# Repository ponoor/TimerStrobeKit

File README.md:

# TimerStrobeKit
A simple Arduino shield for timer and strobe

### BOM list
https://docs.google.com/spreadsheets/d/1uPikIjkAWC3uok0h-zIkFJXL1ukJnj77JqhKgZAHLNc/edit?usp=sharing

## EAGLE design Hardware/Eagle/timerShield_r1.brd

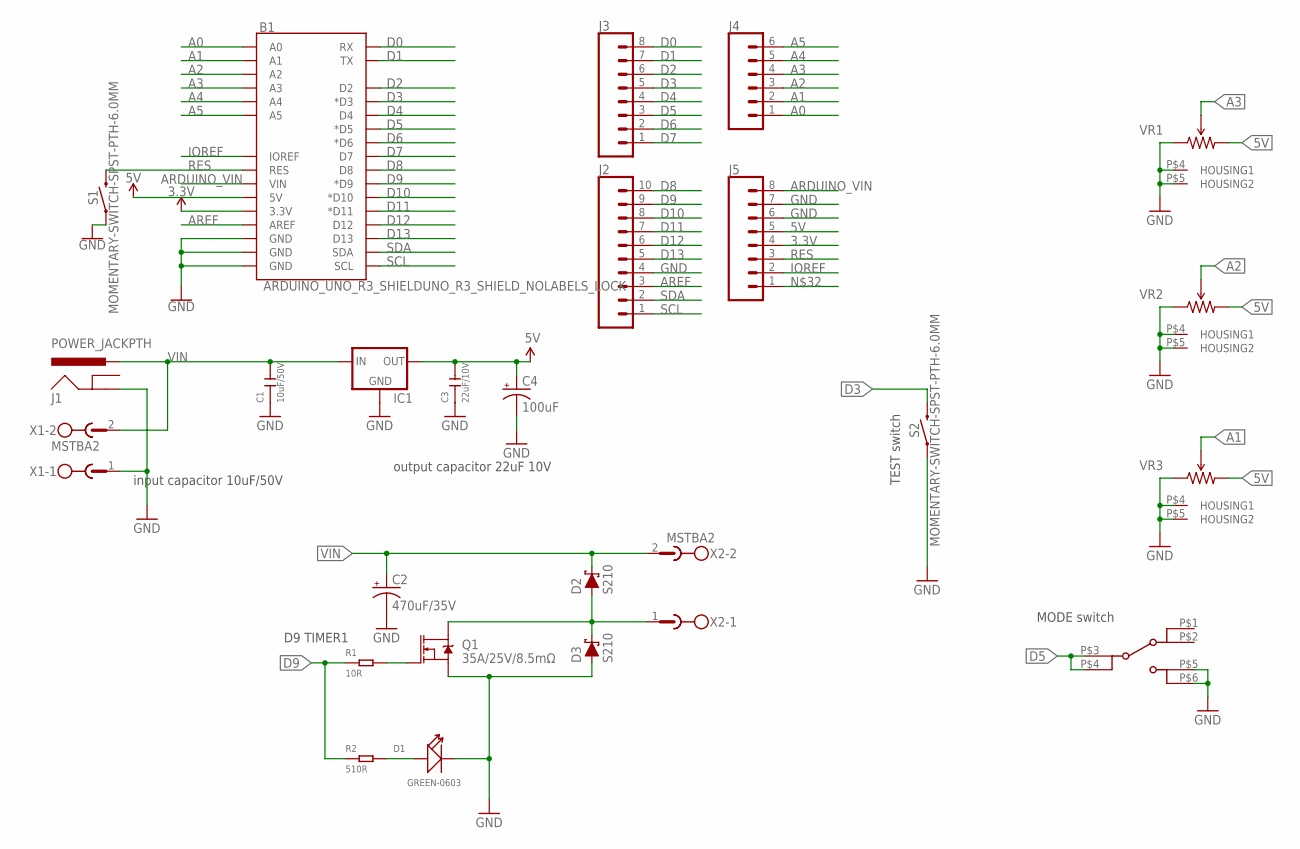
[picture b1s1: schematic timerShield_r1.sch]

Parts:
B1: ARDUINO_UNO_R3_SHIELDUNO_R3_SHIELD_NOLABELS_LOCK; UNO_R3_SHIELD_NOLABELS_LOCK
C1: 10uF/50V; C1206
C2: 470uF/35V; CPOL-RADIAL-5MM-10MM-KIT
C3: 22uF/10V; C0805
C4: 100uF; CPOL-RADIAL-2.5MM-6.5MM
D1: GREEN-0603; LED-0603
D2, D3: S210; SMA-DIODE
IC1: V_REG_78XX_K78XX-500R3; K78XX-500R3
J1: POWER_JACKPTH; POWER_JACK_PTH
J2: CONN_10"; 1X10
J3, J5: CONN_08"; 1X08
J4: CONN_06SILK_FEMALE_PTH; 1X06
MODE: SW_SSSS213202NARROW; SW-SSSS213202NARROW
Q1: 35A/25V/8.5mΩ; DPAK
R1: 10R; R0603
R2: 510R; R0603
S1, S2: MOMENTARY-SWITCH-SPST-PTH-6.0MM; TACTILE_SWITCH_PTH_6.0MM
VR1, VR2, VR3: TRIMVR_HOUSING_RK09; RK09
X1, X2: MSTBA2

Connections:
3.3V: B1.3.3V, J5.4
5V: B1.5V, C3.2, C4.1 (+), IC1.3 (OUT), J5.5, VR1.3 (CW), VR2.3 (CW), VR3.3 (CW)
A0: B1.A0, J4.1
A1: B1.A1, J4.2, VR3.2 (WIPER)
A2: B1.A2, J4.3, VR2.2 (WIPER)
A3: B1.A3, J4.4, VR1.2 (WIPER)
A4: B1.A4, J4.5
A5: B1.A5, J4.6
ARDUINO_VIN: B1.VIN, J5.8
AREF: B1.AREF, J2.3
D0: B1.RX, J3.8
D1: B1.TX, J3.7
D2: B1.D2, J3.6
D3: B1.D3 (*D3), J3.5, S2.3 (2)
D4: B1.D4, J3.4
D5: B1.D5 (*D5), J3.3, MODE.P$3 (2-1), MODE.P$4 (2-2)
D6: B1.D6 (*D6), J3.2
D7: B1.D7, J3.1
D8: B1.D8, J2.10
D9: B1.D9 (*D9), J2.9, R1.1, R2.1
D10: B1.D10 (*D10), J2.8
D11: B1.D11 (*D11), J2.7
D12: B1.D12, J2.6
D13: B1.D13, J2.5
GND: B1.GND@0 (GND), B1.GND@1 (GND), B1.GND@2 (GND), C1.1, C2.-, C3.1, C4.2 (-), D1.-, D3.A, IC1.2 (GND), J1.GND, J2.4, J5.6, J5.7, MODE.P$5 (3-1), MODE.P$6 (3-2), Q1.3 (S), S1.1, S2.1, VR1.1 (CCW), VR1.P$4 (HOUSING1), VR1.P$5 (HOUSING2), VR2.1 (CCW), VR2.P$4 (HOUSING1), VR2.P$5 (HOUSING2), VR3.1 (CCW), VR3.P$4 (HOUSING1), VR3.P$5 (HOUSING2), X1.1
IOREF: B1.IOREF, J5.2
unnamed: Q1.1 (G), R1.2
unnamed: D1.+, R2.2
unnamed: D2.A, D3.C, Q1.4 (D), X2.1
RES: B1.RES, J5.3, S1.3 (2)
SCL: B1.SCL, J2.1
SDA: B1.SDA, J2.2
VIN: C1.2, C2.+, D2.C, IC1.1 (IN), J1.PWR, X1.2, X2.2

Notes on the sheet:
input capacitor 10uF/50V
output capacitor 22uF 10V
D9 TIMER1
MODE switch
TEST switch

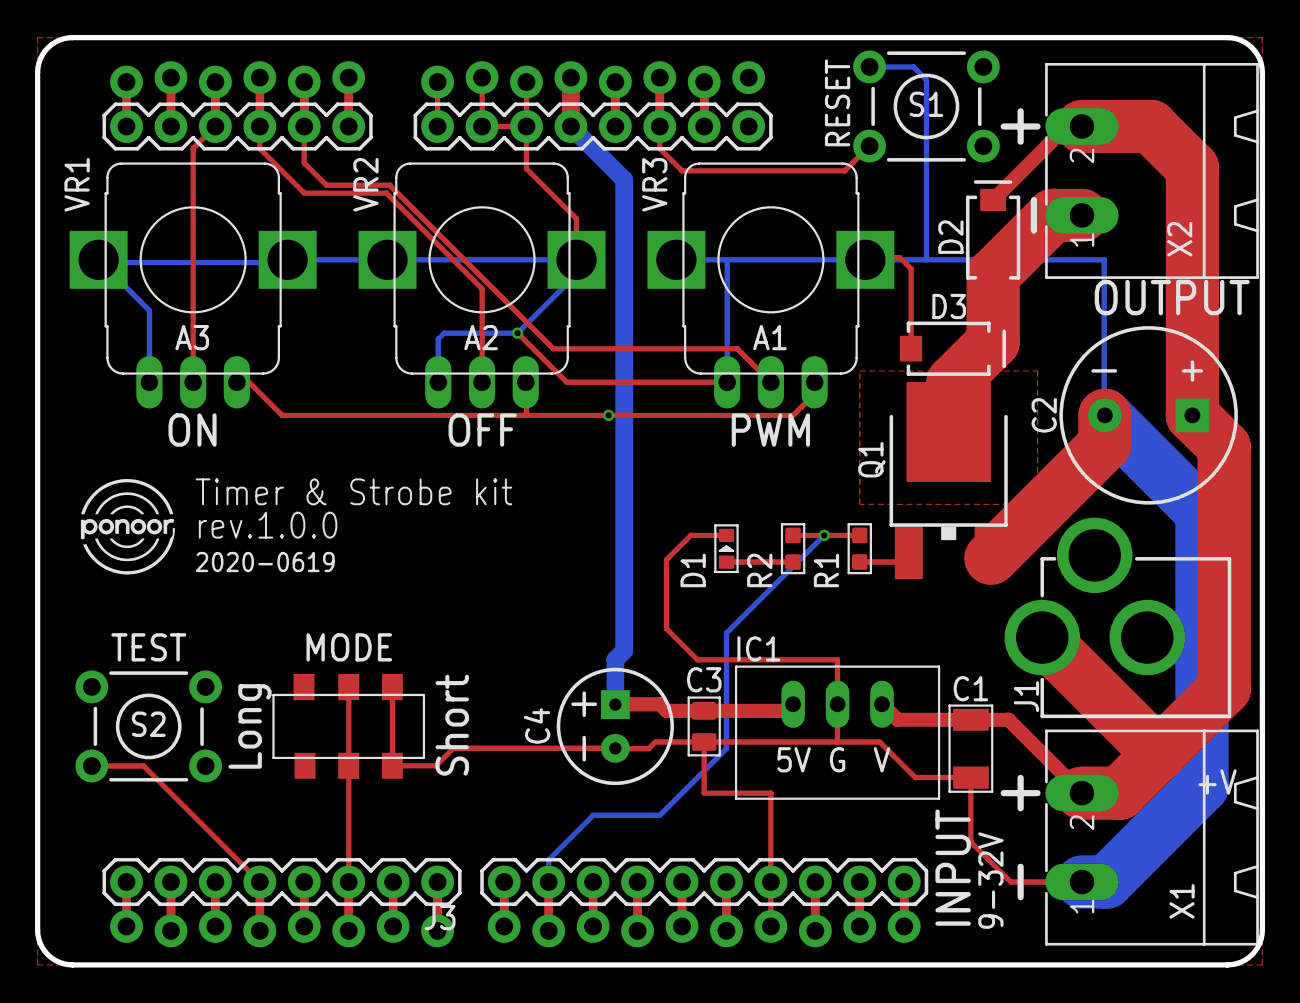
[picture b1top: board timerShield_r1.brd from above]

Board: 2 copper layers, 70.0 x 53.0 mm, 27 parts (1 on the bottom side), 33 nets.

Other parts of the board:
U$1: PONOOR_LOGO_6MM
U$2: PONOOR_TEXT_15MM

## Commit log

2020-07-04 added Eagle files and Arduino code.
2021-07-04 added BOM list
2022-05-23 Added a new firmware (for PIO)
2022-05-27 Correct timer interrupt bug, added exponential curve for a strobe mode
2022-05-31 typo

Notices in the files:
parts and their libraries:
SparkFun-Boards: Licensing: Creative Commons ShareAlike 4.0 International - https://creativecommons.org/licenses/by-sa/4.0
SparkFun: Licensing: CC v3.0 Share-Alike You are welcome to use this library for commercial purposes.
